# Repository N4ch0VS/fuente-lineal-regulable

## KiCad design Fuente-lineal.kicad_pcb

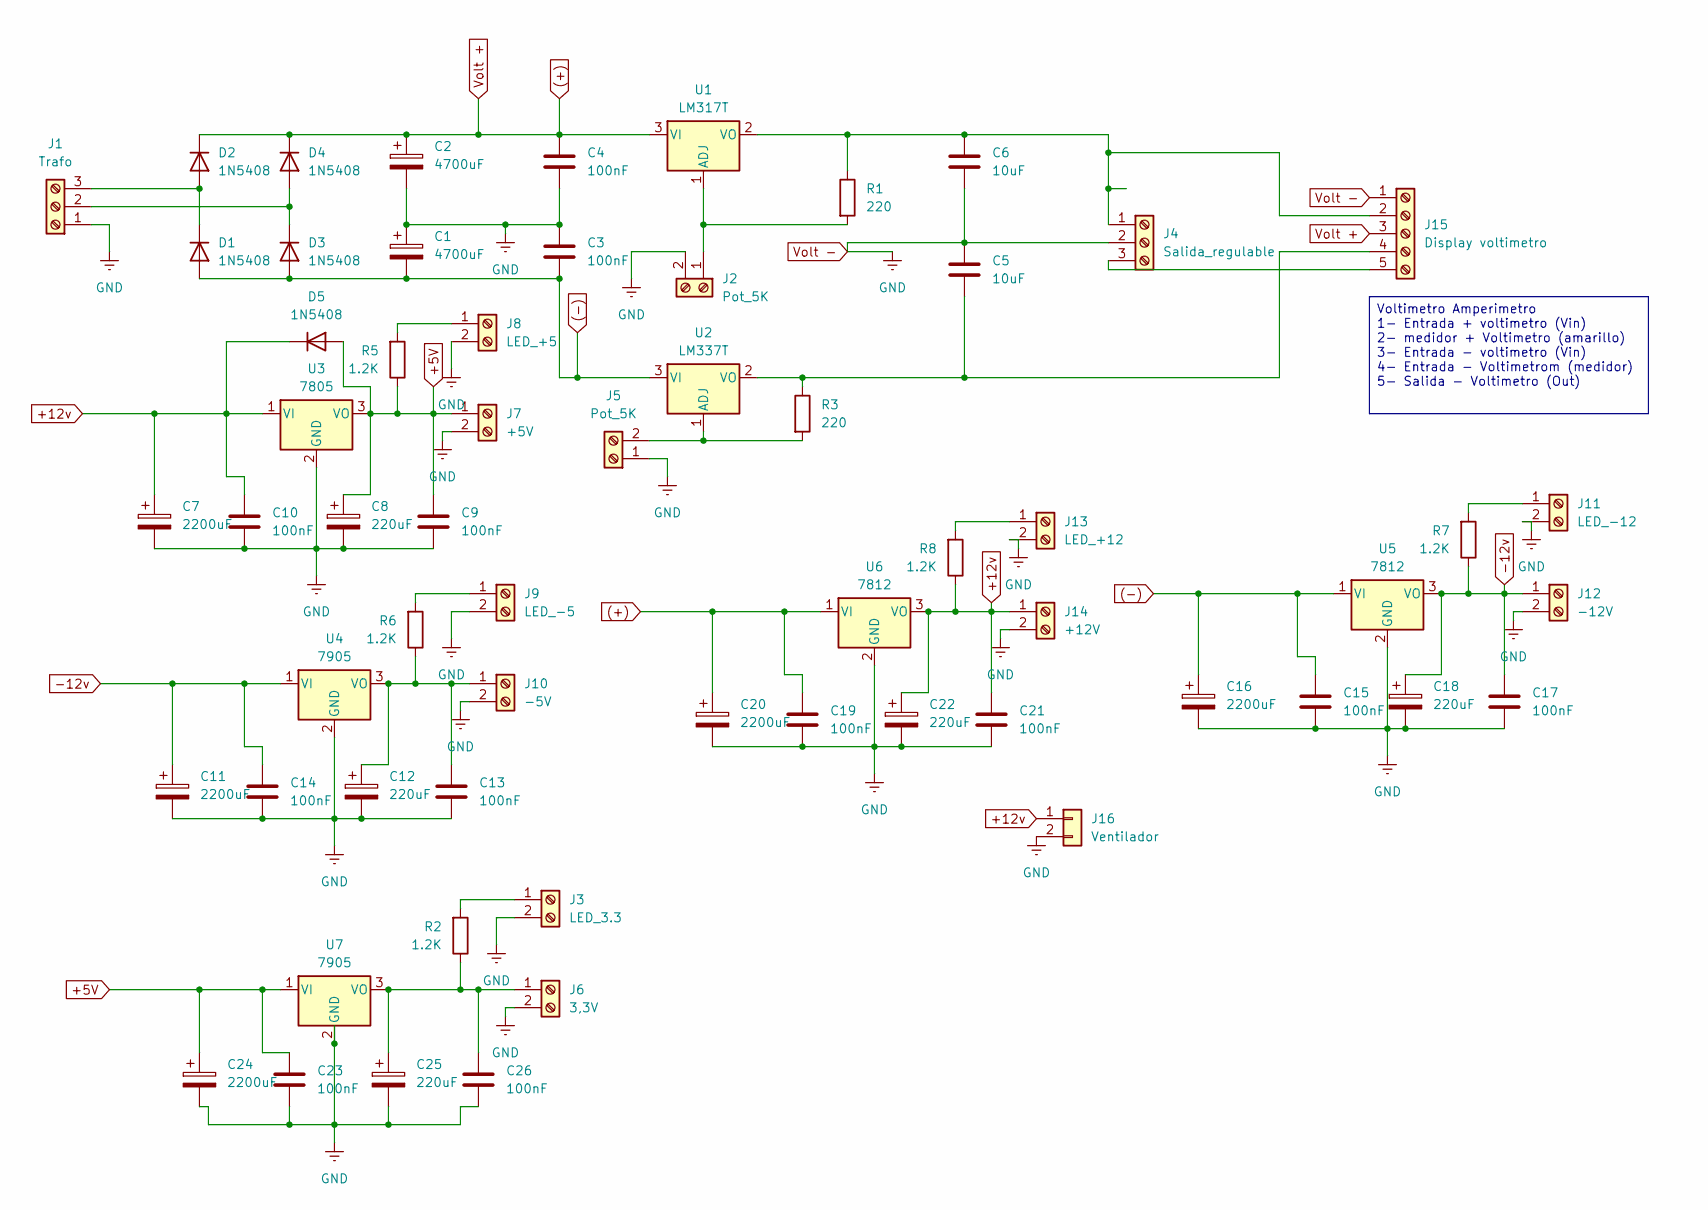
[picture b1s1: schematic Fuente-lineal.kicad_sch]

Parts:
C1, C2: 4700uF; CP_Radial_D8.0mm_P5.00mm
C3, C4, C9, C10, C13, C14, C15, C17, C19, C21, C23, C26: 100nF; C_Disc_D7.0mm_W2.5mm_P5.00mm
C5, C6: 10uF; C_Disc_D7.0mm_W2.5mm_P5.00mm
C7, C11, C16, C20, C24: 2200uF; CP_Radial_D8.0mm_P5.00mm
C8, C12, C18, C22, C25: 220uF; CP_Radial_D8.0mm_P5.00mm
D1, D2, D3, D4, D5: 1N5408; D_5W_P10.16mm_Horizontal
J1: Trafo; TerminalBlock_MaiXu_MX126-5.0-03P_1x03_P5.00mm
J2, J5: Pot_5K; TerminalBlock_Phoenix_PT-1,5-2-5.0-H_1x02_P5.00mm_Horizontal
J3: LED_3.3; PinHeader_1x02_P2.54mm_Vertical
J4: Salida_regulable; TerminalBlock_MaiXu_MX126-5.0-03P_1x03_P5.00mm
J6: 3,3V; TerminalBlock_Phoenix_PT-1,5-2-5.0-H_1x02_P5.00mm_Horizontal
J7: +5V; TerminalBlock_Phoenix_PT-1,5-2-5.0-H_1x02_P5.00mm_Horizontal
J8: LED_+5; PinHeader_1x02_P2.54mm_Vertical
J9: LED_-5; PinHeader_1x02_P2.54mm_Vertical
J10: -5V; TerminalBlock_Phoenix_PT-1,5-2-5.0-H_1x02_P5.00mm_Horizontal
J11: LED_-12; PinHeader_1x02_P2.54mm_Vertical
J12: -12V; TerminalBlock_Phoenix_PT-1,5-2-5.0-H_1x02_P5.00mm_Horizontal
J13: LED_+12; PinHeader_1x02_P2.54mm_Vertical
J14: +12V; TerminalBlock_Phoenix_PT-1,5-2-5.0-H_1x02_P5.00mm_Horizontal
J15: Display voltimetro; TerminalBlock_MaiXu_MX126-5.0-05P_1x05_P5.00mm
J16: Ventilador; PinHeader_1x02_P2.54mm_Vertical
R1, R3: 220; R_Axial_DIN0207_L6.3mm_D2.5mm_P10.16mm_Horizontal
R2, R5, R6, R7, R8: 1.2K; R_Axial_DIN0207_L6.3mm_D2.5mm_P10.16mm_Horizontal
U1: LM317T; TO-220-3_Vertical
U2: LM337T; TO-220-3_Vertical
U3: 7805; TO-220-3_Vertical
U4, U7: 7905; TO-220-3_Vertical
U5, U6: 7812; TO-220-3_Vertical

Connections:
(+): C2.1, C4.1, C19.1, C20.1, D2.1 (K), D4.1 (K), J15.3, U1.3 (VI), U6.1 (VI)
(-): C1.2, C3.2, C15.1, C16.1, D1.2 (A), D3.2 (A), U2.3 (VI), U5.1 (VI)
+5V: C8.1, C9.1, C23.1, C24.1, D5.2 (A), J7.1, R5.1, U3.3 (VO), U7.1 (VI)
+12v: C7.1, C10.1, C21.1, C22.1, D5.1 (K), J14.1, J16.1, R8.1, U3.1 (VI), U6.3 (VO)
-12v: C11.1, C14.1, C17.1, C18.1, J12.1, R7.1, U4.1 (VI), U5.3 (VO)
unnamed: D1.1 (K), D2.2 (A), J1.3
unnamed: D3.1 (K), D4.2 (A), J1.2
unnamed: J2.1, R1.2, U1.1 (ADJ)
unnamed: J3.1, R2.2
unnamed: J5.2, R3.2, U2.1 (ADJ)
unnamed: C25.1, C26.1, J6.1, R2.1, U7.3 (VO)
unnamed: J8.1, R5.2
unnamed: J9.1, R6.2
unnamed: C12.1, C13.1, J10.1, R6.1, U4.3 (VO)
unnamed: J11.1, R7.2
unnamed: J13.1, R8.2
unnamed: C6.1, J4.1, J15.2, R1.1, U1.2 (VO)
unnamed: C5.2, J15.4, R3.1, U2.2 (VO)
unnamed: J4.3, J15.5
Volt -: C1.1, C2.2, C3.1, C4.2, C5.1, C6.2, C7.2, C8.2, C9.2, C10.2, C11.2, C12.2, C13.2, C14.2, C15.2, C16.2, C17.2, C18.2, C19.2, C20.2, C21.2, C22.2, C23.2, C24.2, C25.2, C26.2, J1.1, J2.2, J3.2, J4.2, J5.1, J6.2, J7.2, J8.2, J9.2, J10.2, J11.2, J12.2, J13.2, J14.2, J15.1, J16.2, U3.2 (GND), U4.2 (GND), U5.2 (GND), U6.2 (GND), U7.2 (GND)

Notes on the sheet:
Voltimetro Amperimetro 1- Entrada + voltimetro (Vin) 2- medidor + Voltimetro (amarillo) 3- Entrada - voltimetro (Vin) 4- Entrada - Voltimetrom (medidor) 5- Salida - Voltimetro (Out)

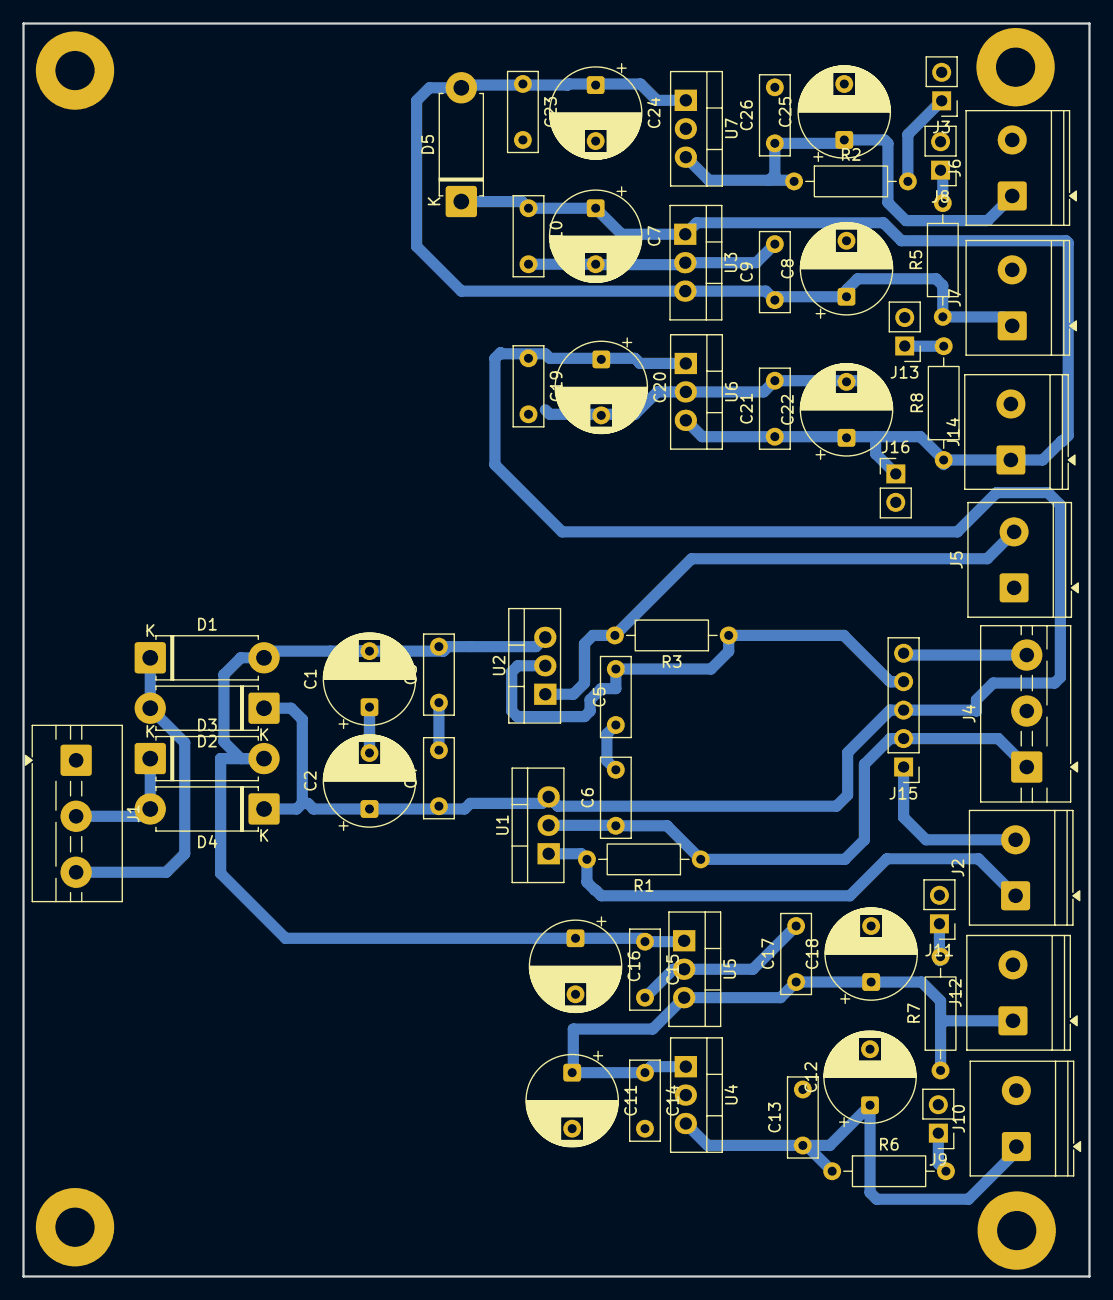
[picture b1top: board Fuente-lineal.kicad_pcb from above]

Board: 2 copper layers, 95.2 x 111.9 mm, 61 parts (0 on the bottom side), 20 nets.

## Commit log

2026-05-12 Initial commit: KiCad fuente lineal regulable project
